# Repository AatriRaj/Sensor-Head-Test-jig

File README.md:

# Sensor-Head-Test-jig
It is used to test a combined sensor pcb board which comprises of 8 TMAG sensors and 4 eddy current coil sensor . It has 3 subsheet schematics which are as follows :-

1- UC(micro controller) BLOCK-: It comprises of RP2040 and a flash memory ic (W25Q16JJVUXIQ_TR) . This block is used for control of I/0 signals and power signals . <br />

2- LVDS TX BLOCK -: It consists of a Low Voltage Differential Signal IC (SN65LVDT41QPWREP) to communicate with the reciever IC present on Combined Sensor head pcb.<br />

3- USB BLOCK -: It consists of a Type-C USB Receptacle 2.0 and a 5V TO 3.3V converter IC (LD39200PU33R) to supply power for the uc block .  <br />

Routing screenshot-:

3d view screenshot-:

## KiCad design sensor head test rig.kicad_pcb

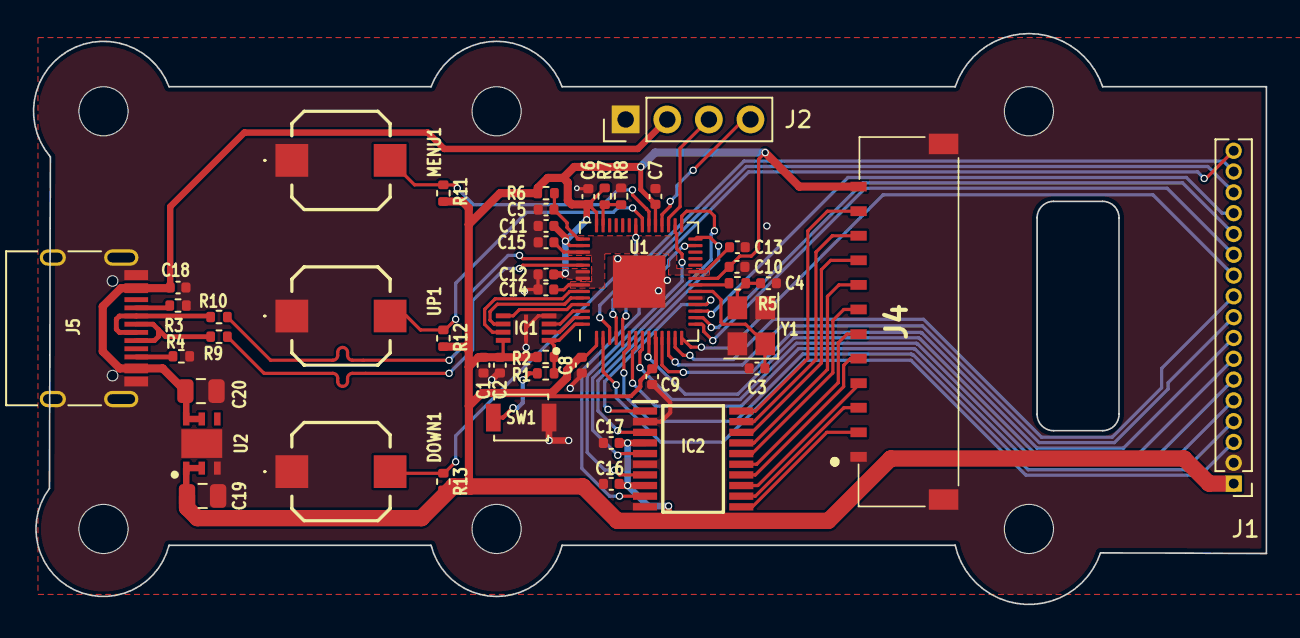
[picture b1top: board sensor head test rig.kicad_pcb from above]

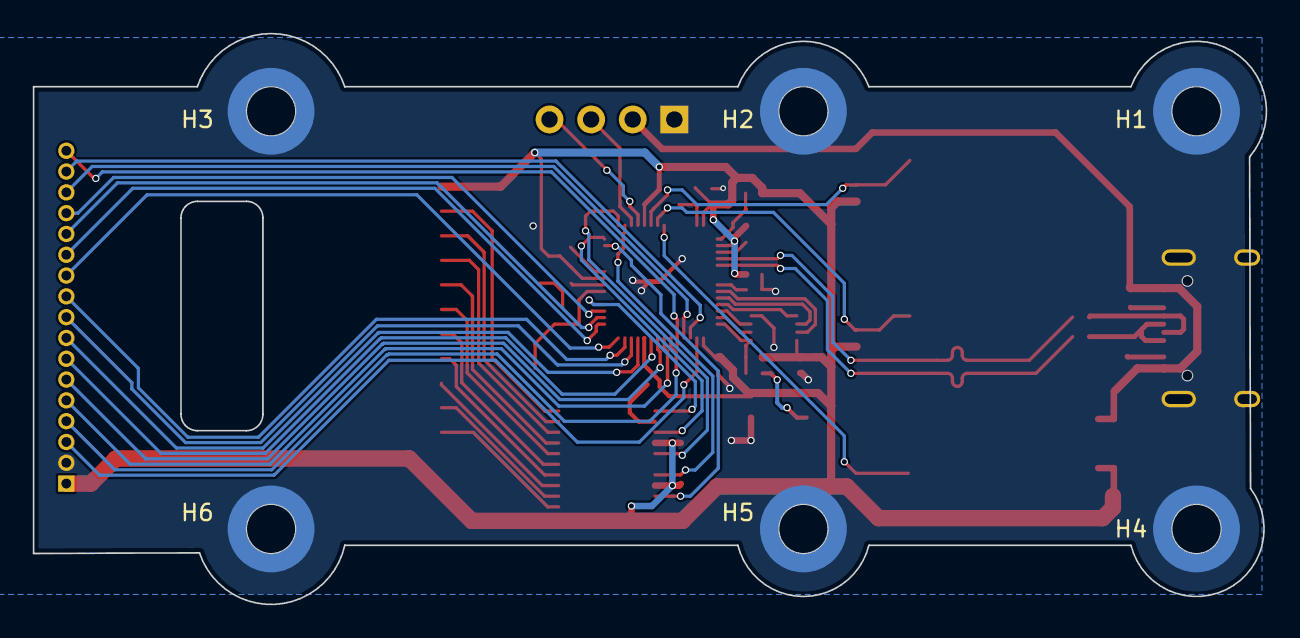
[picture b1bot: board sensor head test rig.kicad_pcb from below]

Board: 2 copper layers, 75.3 x 34.8 mm, 52 parts (6 on the bottom side), 57 nets.

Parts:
C1, C5, C6, C7, C8, C9, C10, C11, C13, C14, C16, C18: 0.1uF; C_0402_1005Metric
C2, C12, C15: 2.2uF; C_0402_1005Metric
C3, C4: 15pF; C_0402_1005Metric
C17: 0.001uF; C_0402_1005Metric
C19, C20: 10uF 10V; C_0805_2012Metric
DOWN1: 430133050816
H1, H2, H3, H4, H5, H6: MountingHole_Pad; Mounting_Wuerth_WA-SMSI-M2_H2mm_9774020243
IC1: W25Q16JVUXIQ_TR; SON50P300X200X60-9N
IC2: SN65LVDT41QPWREP; SOP65P640X120-20N
J1: Conn_01x17; PinHeader_1x17_P1.27mm_Vertical-modified
J2: Conn_01x04; PinHeader_1x04_P2.54mm_Vertical
J4: 504050-1291; 5040501291
J5: USB_C_Receptacle_USB2.0; USB_C_Receptacle_HRO_TYPE-C-31-M-12
MENU1: 430133050816
R1, R5: 1K; R_0402_1005Metric
R2: 10K; R_0402_1005Metric
R3, R4: 5.1k; R_0402_1005Metric
R6: 1R; R_0402_1005Metric
R7, R8: 200K; R_0402_1005Metric
R9, R10: 27R; R_0402_1005Metric
R11, R12, R13: 10k; R_0402_1005Metric
SW1: Boot SW; SW_SPST_B3U-1000P
U1: RP2040; QFN-56-1EP_7x7mm_P0.4mm_EP3.2x3.2mm
U2: LD39200PU33R; SON95P300X300X100-7N-D
UP1: 430133050816
Y1: ABM8-12.000MHZ-12-B1U-T; Crystal_SMD_3225-4Pin_3.2x2.5mm

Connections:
+1V1: C13.1, C14.1, C15.1, U1.23 (DVDD), U1.45 (VREG_VOUT), U1.50 (DVDD)
+3.3V: C1.1, C2.1, C6.1, C7.1, C8.1, C9.1, C10.1, C11.1, C12.1, C16.1, C17.1, C19.1, IC1.8 (VCC), IC2.4 (VCC_1), IC2.8 (VCC_2), J1.1, J4.12, R2.1, R6.1, R7.2, R11.2, R12.2, R13.2, U1.1 (IOVDD), U1.10 (IOVDD), U1.22 (IOVDD), U1.33 (IOVDD), U1.42 (IOVDD), U1.44 (VREG_IN), U1.48 (USB_VDD), U1.49 (IOVDD), U2.1 (OUT), U2.2 (ADJ/SENSE)
+5V: C18.1, C20.1, J2.2, J5.A4 (VBUS), J5.A9 (VBUS), J5.B4 (VBUS), J5.B9 (VBUS), U2.5 (EN), U2.6 (IN)
/LVDS TX BLOCK/1Y: IC2.20 (1Y), J4.11
/LVDS TX BLOCK/1Z: IC2.19 (1Z), J4.10
/LVDS TX BLOCK/2Y: IC2.18 (2Y), J4.9
/LVDS TX BLOCK/2Z: IC2.17 (2Z), J4.8
/LVDS TX BLOCK/3Y: IC2.16 (3Y), J4.7
/LVDS TX BLOCK/3Z: IC2.15 (3Z), J4.6
/LVDS TX BLOCK/4Y: IC2.14 (4Y), J4.5
/LVDS TX BLOCK/4Z: IC2.13 (4Z), J4.4
/LVDS TX BLOCK/5A: IC2.12 (5A), J4.3
/LVDS TX BLOCK/5B: IC2.11 (5B), J4.2
/LVDS TX BLOCK/RX1: IC2.9 (5R), U1.27 (GPIO16)
/LVDS TX BLOCK/TX1: IC2.1 (1D), U1.18 (GPIO15)
/LVDS TX BLOCK/TX2: IC2.3 (2D), U1.28 (GPIO17)
/LVDS TX BLOCK/TX3: IC2.5 (3D), U1.29 (GPIO18)
/LVDS TX BLOCK/TX4: IC2.7 (4D), U1.30 (GPIO19)
/USB BLOCK/D+: J5.A6 (D+), J5.B6 (D+), R9.1
/USB BLOCK/D-: J5.A7 (D-), J5.B7 (D-), R10.1
/uc block/ADC_AVDD: C5.1, R6.2, U1.43 (ADC_AVDD)
/uc block/Boot: R1.1, SW1.1
/uc block/CS1: J1.14, U1.17 (GPIO14)
/uc block/CS2: J1.13, U1.16 (GPIO13)
/uc block/CS3: J1.12, U1.15 (GPIO12)
/uc block/CS4: J1.11, U1.14 (GPIO11)
/uc block/CS5: J1.10, U1.13 (GPIO10)
/uc block/CS6: J1.9, U1.12 (GPIO9)
/uc block/CS7: J1.8, U1.11 (GPIO8)
/uc block/CS8: J1.7, U1.9 (GPIO7)
/uc block/CS9: J1.6, U1.8 (GPIO6)
/uc block/CS10: J1.5, U1.7 (GPIO5)
/uc block/CS11: J1.4, U1.6 (GPIO4)
/uc block/CS12: J1.3, U1.2 (GPIO0)
/uc block/GPIO_29: R7.1, R8.2, U1.41 (GPIO29_ADC3)
/uc block/QSPI_0: IC1.5 (DI(IO0)), U1.53 (QSPI_SD0)
/uc block/QSPI_1: IC1.2 (DO(IO1)), U1.55 (QSPI_SD1)
/uc block/QSPI_2: IC1.3 (IO2), U1.54 (QSPI_SD2)
/uc block/QSPI_3: IC1.7 (IO3), U1.51 (QSPI_SD3)
/uc block/QSPI_CLK: IC1.6 (CLK), U1.52 (QSPI_SCLK)
/uc block/QSPI_CS: IC1.1 (~CS), R1.2, R2.2, U1.56 (QSPI_SS)
/uc block/SCK: J1.15, U1.4 (GPIO2)
/uc block/SCL: J2.4, U1.32 (GPIO21)
/uc block/SDA: J2.3, U1.31 (GPIO20)
/uc block/SDI: J1.17, U1.5 (GPIO3)
/uc block/SDO: J1.16, U1.3 (GPIO1)
/uc block/SW1: MENU1.2, R11.1, U1.34 (GPIO22)
/uc block/SW2: R12.1, U1.35 (GPIO23), UP1.2
/uc block/SW3: DOWN1.2, R13.1, U1.36 (GPIO24)
GND: C1.2, C2.2, C3.2, C4.2, C5.2, C6.2, C7.2, C8.2, C9.2, C10.2, C11.2, C12.2, C13.2, C14.2, C15.2, C16.2, C17.2, C18.2, C19.2, C20.2, DOWN1.1, H1.1, H2.1, H3.1, H4.1, H5.1, H6.1, IC1.4 (GND), IC1.9 (EP), IC2.2 (GND_1), IC2.6 (GND_2), IC2.10 (GND_3), J1.2, J2.1, J4.1, J4.MP1, J4.MP2, J5.A1 (GND), J5.A12 (GND), J5.B1 (GND), J5.B12 (GND), J5.S1 (SHIELD), MENU1.1, R3.2, R4.2, R8.1, SW1.2, U1.19 (TESTEN), U1.57 (GND), U2.3 (GND), U2.7 (EPAD), UP1.1, Y1.2, Y1.4
unnamed: C4.1, R5.1, Y1.3
unnamed: J5.A5 (CC1), R3.1
unnamed: J5.B5 (CC2), R4.1
unnamed: R10.2, U1.46 (USB_DM)
unnamed: R9.2, U1.47 (USB_DP)
unnamed: C3.1, U1.20 (XIN), Y1.1
unnamed: R5.2, U1.21 (XOUT)
